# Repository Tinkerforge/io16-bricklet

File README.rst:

IO-16 Bricklet
==============

This repository contains the firmware source code and the hardware design
files. The documentation generator configs can be found at
https://github.com/Tinkerforge/generators

Repository Content
------------------

software/:
 * examples/: Examples for all supported languages
 * build/: Compiled files
 * src/: Source code of firmware
 * Makefile: Makefile to build project

hardware/:
 * Contains KiCad project files and additionally schematics as PDF

datasheets/:
 * Contains datasheets for sensors and complex ICs that are used

Hardware
--------

The hardware is designed with the open source EDA Suite KiCad
(http://www.kicad.org). Before you are able to open the files,
you have to install the Tinkerforge kicad-libraries
(https://github.com/Tinkerforge/kicad-libraries). You can either clone
them directly in hardware/ or clone them in a separate folder and
symlink them into hardware/
(ln -s kicad_path/kicad-libraries project_path/hardware). After that you
can open the .pro file in hardware/ with KiCad and from there view and
modify the schematics and the PCB layout.

Software
--------

If you want to do your own Brick/Bricklet firmware development we highly
recommend that you use our build environment setup script and read the
tutorial (https://www.tinkerforge.com/en/doc/Tutorials/Tutorial_Build_Environment/Tutorial.html).

To compile the C code we recommend you to install the newest GNU Arm Embedded
Toolchain (https://launchpad.net/gcc-arm-embedded/+download).
You also need to install bricklib (https://github.com/Tinkerforge/bricklib)
and brickletlib (https://github.com/Tinkerforge/brickletlib).

You can either clone it directly in software/src/ or clone it in a
separate folder and symlink it into software/src/
(ln -s bricklib_path/bricklib project_path/software/src/ and
ln -s brickletlib_path/brickletlib project_path/software/src/).
Finally make sure to have CMake installed
(http://www.cmake.org/cmake/resources/software.html).

After that you can build the firmware by invoking make in software/.
The firmware (.bin) can then be found in software/build/ and uploaded
with brickv (click button "Flashing" on start screen).

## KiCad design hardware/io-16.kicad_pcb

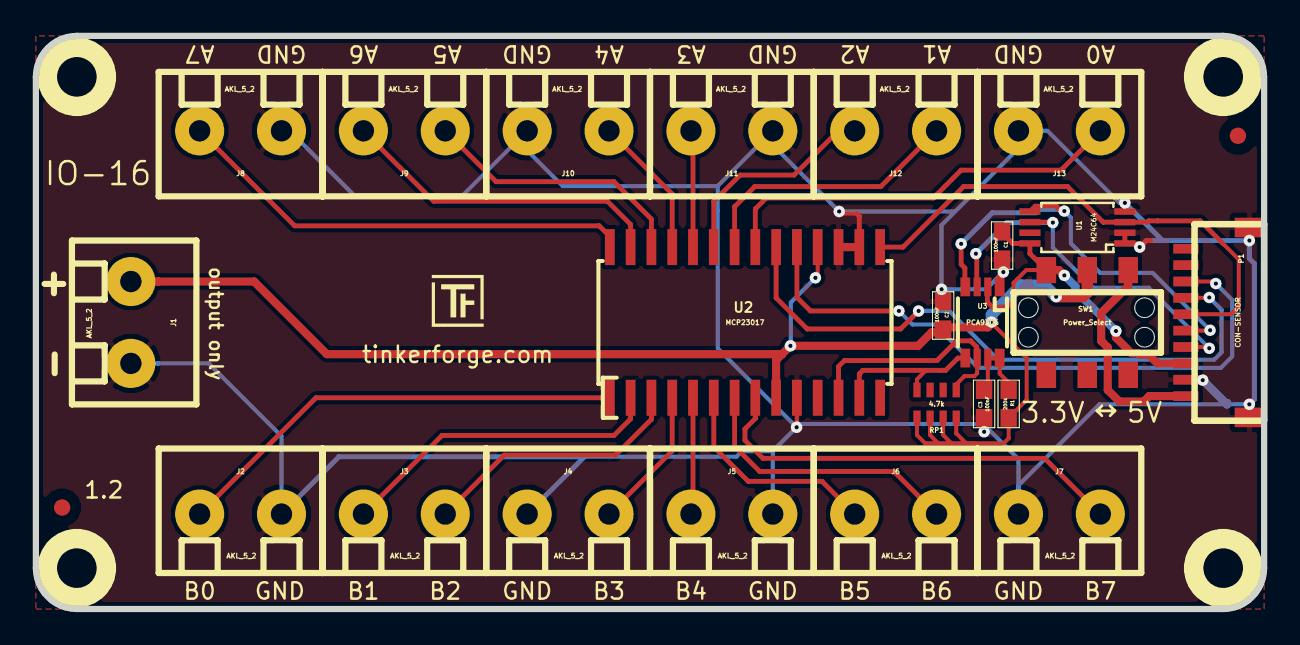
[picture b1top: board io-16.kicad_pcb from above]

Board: 2 copper layers, 75.0 x 35.0 mm, 32 parts (0 on the bottom side), 28 nets.

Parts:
C1, C2, C3: 100nF; 0603E
Fiducial_Mark: VAL**; Fiducial_Mark
Fiducial_Mark#2: VAL**; Fiducial_Mark
J1, J2, J3, J4, J5, J6, J7, J8, J9, J10, J11, J12, J13: AKL_5_2
P1: CON-SENSOR
R1: 200k; 0603E
RP1: 4.7k; 4X0603
Ref**: Val**; Logo_31x31
SW1: Power_Select; SLIDE_SWITCH
U1: M24C64; TSSOP8
U2: MCP23017; SOIC28
U3: PCA9306; TSSOP8_3
U4, U5, U6, U7: DRILL; DRILL_NP
VAL: WEEE_7mm
VAL#2: CE_5mm

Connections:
GND: C1.1, C2.2, C3.2, J1.1, J2.1, J4.2, J5.1, J7.2, J8.2, J10.1, J11.2, J13.1, P1.2, P1.EP, U1.1, U1.2, U1.4, U2.10, U2.16, U2.17, U3.1
IN_1: P1.7, U2.20
IN_2: P1.8, U2.19
unnamed: C3.1, R1.2, U3.7, U3.8
unnamed: J2.2, U2.1
unnamed: J3.1, U2.3
unnamed: J3.2, U2.2
unnamed: J4.1, U2.4
unnamed: J5.2, U2.5
unnamed: J6.1, U2.7
unnamed: J6.2, U2.6
unnamed: J7.1, U2.8
unnamed: J8.1, U2.28
unnamed: J9.1, U2.27
unnamed: J9.2, U2.26
unnamed: J10.2, U2.25
unnamed: J11.1, U2.24
unnamed: J12.1, U2.23
unnamed: J12.2, U2.22
unnamed: J13.2, U2.21
unnamed: P1.1, SW1.1
SCL: P1.4, U1.6, U3.3
SCL2: RP1.8, U2.12, U3.6
SDA: P1.5, U1.5, U3.4
SDA2: RP1.5, U2.13, U3.5
SEL: P1.6, U1.3, U2.15
VAA: C2.1, J1.2, R1.1, RP1.1, RP1.2, RP1.3, RP1.4, SW1.2, U2.9, U2.18
VCC: C1.2, P1.3, SW1.3, U1.8, U3.2

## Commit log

2011-08-25 initial hardware source commit
2011-08-25 add project description
2011-09-13 fix typo in examples
2011-09-13 add java bindings and examples
2011-09-14 limit line length of java examples to 100 characters
2011-09-23 Add C# examples and bindings
2011-09-23 Add C# bindings
2011-10-05 Remove Bindings and IP Connection (these are generated and they change too often) and rename bindings to examples
2011-10-05 add tinkerforge package to python imports
2011-10-06 remove faulty gcc commandline invocation
2011-10-06 add firmware version and name
2012-02-13 checkin of version V1.1 - remove resistor in address line - add fiducials on board
2012-02-14 add compatability for different tick types
2012-02-14 calculation and message together in one tick task if necessary
2012-02-15 Add changelog
2012-02-15 Move software changelog to software folder
2012-03-16 Save and compare last interrupt (for better bounce detection)
2012-04-25 Unify capitalization of "IP connection" in examples
2012-05-09 Add PHP examples
2012-05-14 java: Remove unnecessary new String(...) calls
2012-05-25 Add Ruby examples
2012-06-05 Fix register_callback syntax error in Ruby examples on Windows
2012-06-12 Use correct term 'Bricklet' in example code error message
2012-06-12 Prefer IPConnection destroy over join_thread
2012-07-01 Add generate_makefile.bat for windows
2012-07-23 Register callback before enabling interrupt in all examples
2012-07-25 Add Delphi examples
2012-08-01 Add monoflop functionality
2012-08-07 Avoid useless I2C reads during monoflop handling
2012-08-08 delphi: Add comment about UID
2012-09-07 Fix I2C low address comment
2012-09-07 Ignore temporary build files
2012-10-04 Extend .gitignore
2012-10-24 Make cmake find the correct objcopy binary
    On some systems cmake uses the wrong objcopy binary, tell it to use
    the correct one.
2012-11-13 Support for protocol 2.0
2012-11-29 Make examples compatible to Protocol V2.0
2012-11-29 Make Ruby examples Protocol 2.0 compatible
2012-11-29 Make C examples Protocol 2.0 compatible
2012-11-29 Make Java examples Protocol 2.0 compatible
2012-11-29 Make PHP examples Protocol 2.0 compatible
2012-11-29 Make Delphi/Pascal examples Protocol 2.0 compatible
2012-11-30 Fix invalid parameter checks
2012-11-30 delphi: Remove unnecessary parentheses and call destructor again
2012-12-05 Add protocol 2.0 compatability to C# bindings
2012-12-06 Fix C example
2012-12-11 Avoid g++ warnings about missing casts in C examples
2013-01-09 Use specific device object for callbacks
2013-01-14 Add possibility to set selected values to API
2013-01-17 Make Java examples compatible to new listener approach
2013-02-07 Use IPconnection disconnect explicitly in examples
2013-02-18 Add Visual Basic .NET examples
2013-03-01 Add missing invocation for set_selected_values function
2013-05-27 Apply debounce period on port b again
2013-08-12 Add shell examples
2013-08-16 shell: Fix syntax error
2013-08-21 windows: Don't trigger a build in generate_makefile.bat
    Also use normal make instead of a special named one.
2013-08-28 Add edge counters for pin 0 on both ports
2013-09-02 Fix edge count bug and save space to compile with O2
2013-09-02 Add changelog for 2.0.4
2014-01-10 Add Perl examples
2014-01-15 php: Use const for constant values
2014-02-07 Add Mathematica examples
2014-02-10 perl: fixed namespace
2014-02-12 javascript: add examples
2014-02-18 javascript: examples fixed
2014-02-20 Fix direction_mask return of get_port_configuration and use correct internal register in set_selected_values
2014-02-20 javascript: add html examples
2014-02-24 javascript: port 4280, startExample()
2014-02-28 javascript: Break long lines and cleanup whitespace
2014-03-05 Add LabVIEW examples
2014-03-06 labview: Add examples in LV2010 format
2014-03-27 matlab: add example
2014-04-02 java: Unify constants style
2014-04-02 perl: Unify print style
2014-04-17 matlab: Adapt examples to new callback style
2014-04-17 matlab: Add parentheses to make pygments happy
2014-07-15 java: Replace System.console() usage with an Eclipse compatible pattern
2014-12-02 Use ReadLine instead of ReadKey for C# example
2015-02-13 vbnet: Use ReadLine instead of ReadKey
    Because ReadKey doesn't work with a pipe as stdin on the RED Brick.
2015-03-02 windows: Stop cmake from searching for mingw32-make.exe
    Using MinGW Makefiles as generator makes cmake search for mingw32-make.exe
    which might not be installed because GnuWin32's make.exe is used instead.
2015-03-26 checkin current hardware files
2015-04-09 c: Whitespace
2015-06-18 Break long lines in examples
2015-06-24 javascript: Clean up output creation
2015-06-29 octave: Handle short difference between Octave 3.6 and 3.8
    In Octave 3.6 a short is not automatically handled as a number.
2015-07-23 Make JavaScript browser example textarea readonly
2015-07-27 Cleanup C/C++, C#, Java, Python and Ruby examples
2015-07-29 Reformat changelog
2015-08-07 Use full device class name in Python examples
2015-08-12 Fix minor warnings in C/C++ examples
2015-08-14 Cleanup Delphi examples
2015-08-18 Cleanup VB.NET examples
2015-08-19 Cleanup Perl examples
2015-09-09 Duplicate cmake call to fix bug during cmake creation
2015-09-18 Generator based example cleanup
2015-09-30 Add simple input mode example
2015-09-30 Improve callback handling in shell example
2015-11-12 matlab: Fix callback handling for R2014a
    http://undocumentedmatlab.com/blog/matlab-callbacks-for-java-events-in-r2014a
2015-11-25 Include date and commit into changelog
2015-11-25 Fix typos
2015-11-30 vbnet: Shorten long line
2016-05-18 c: Add missing device destroy call
2016-06-01 Always check IODIR register for port A in edge counter
    Because the edge counter is attached to the first and second pin of port A.
2016-06-01 Clear edge counter flag after updating the edge counter
    Otherwise the edge counter will be updated every tick even if there
    was no edge at all.
2016-06-02 Fix race condition in interrupt detection
    The INT_A and INT_B pins are used to detect interrupts. Reading the GPIO
    registers clears the interrupt condition.
    Before, interrupts were only detected using the INT_A and INT_B pins in
    the tick. But this is racy, because a get_port call would read the GPIO
    register, clearing a potential interrupt condition, before the tick could
    detect it. This results in lost interrupt callbacks.
2016-06-03 Update changelog and version
2016-06-03 Add changelog commit after the fact
2016-06-29 Whitespace
2016-07-01 Make the change UID comment more explicit
2016-07-14 Remove accidentially committed file
2017-01-04 update footprints, drc
2017-01-04 add missing board file
2017-04-13 csharp: Adapt example
2017-04-20 shell: Adapt example
2017-05-12 delphi: Use correct format string
2017-06-02 octave: Use javaObject instead of deprecated java_new
2017-08-01 Add 3d information (final)
2017-08-01 Add 3d model (*.step & *.FCStd)
2017-11-30 Update examples from generator
2017-12-07 mathematica: Also generate .nb files
2018-01-26 c: Fine-tune printf format
2018-02-19 javascript: Close div tag correctly
2018-02-20 Cleanup KiCad libraries config
    Ensure LibDir=kicad-libraries and LibName1=tinkerforge.
    Remove special library.
2018-05-11 Rename files
2018-05-24 perl: Use strict in examples
2018-07-11 Add Makefile with docker support
2018-07-11 Update directory structure and build instructions
2018-07-11 Remove obsolete generate_makefile scripts
2018-11-06 Add rust examples
2018-11-07 rust: Accept host names for ip connection, fix naming inconsistencies
2018-11-07 rust: Rename callback receivers.
2018-12-14 Add go examples.
2018-12-18 go: Change import path.
2018-12-18 go: Change import path again.
2018-12-20 rust: Reformat examples.
2019-01-24 mqtt: Add examples.
2019-01-24 mqtt: Fix example header.
2019-01-24 mqtt: Remove executable bit in example permissions.
2019-01-24 go: Minor example fixes.
2019-01-24 mqtt: Minor example fixes.
2019-03-25 mqtt: Fix example whitespace.
2019-03-28 mqtt: Fix whitespace.
2019-08-22 c: Adapt to bindings changes
2020-01-13 examples: Use python3 input instead of python2 raw_input.
2020-01-13 examples: mqtt: Remove trailing whitespace.
2020-01-14 examples: Update.
2020-04-07 examples: rust: Always block when calling bindings functions.
2021-05-06 examples: Get port B as well
2021-05-06 examples: Avoid variable name collision
2021-10-25 Update KiCad link
    https://www.kicad.org/blog/2021/10/Avoid-links-to-former-kicad-domain/
2022-07-06 Add license files.

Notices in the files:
hardware/io-16.kicad_pcb:
Licensed under CERN OHL v.1.1
Copyright (©) 2011, B.Nordmeyer
Copyright Tinkerforge GmbH 2012.
This documentation describes Open Hardware and is licensed under the
CERN OHL v. 1.1.
